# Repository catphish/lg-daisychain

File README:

PLEASE NOTE: THIS PROJECT HAS BEEN REPLACED BY https://github.com/catphish/ti-daisychain-bms

BMS and CAN interface for bq76PL455A
====================================

This module permits batteries with bq76PL455A based slave boards to be balanced and monitored. Communication
with the battery slave modules takes place via the proprietary daisychain interface on each battery module.
Up to 16 batteries can be connected in a chain.

The module supports the following functionality:
* Automatic balancing of all cells in the chain
* Pack and cell voltages transmitted on CAN bus
* Temperatures transmitted via CAN bus
* Balancing target can be set via CAN or standalone

Standlone Balancing
===================

With jumper CONF2 open, the module will operate in standalone balancing mode. It will regularly monitor the
voltage of all attached cells, and will bleed any cell that meets BOTH of the following conditions.

* Voltage exceeds 4.0V
* Voltage is more than 10mV higher than the voltage of the lowest cell in the pack

For thermal safety, only one cell (wit the highest voltage) per battery will be discharged at a time.

CAN Balancing
=============

With jumper CONF2 closed, balancing is controlled by CAN bus messages. The module will bleed all cells
in the pack that exceed the voltage specified in the appropriate CAN message. Balancing halts after one
second, so messages must be received at least once per second to ensure continuous balancing. CAN messages
are docuented below.

For thermal safety, only one cell (wit the highest voltage) per battery will be discharged at a time.

Monitoring
==========

In all operating modes, the total pack voltage, individual cell voltages, and battery temperatures
are transmitted on the CAN bus. This can be used for external monitoring or to allow a third party
control unit to make decisions about balancing, charging, and safety limits. CAN messages are
docuented below.

Connections
===========

The following connections should be made. Each pair of wires should be twisted together (approx 360 degrees per inch).

1.CANL - Connect this to your CAN bus. On early boards this is mislabeled CANH.
2.CNAH - Connect this to your CAN bus. On early boards this is mislabeled CANL.
3.+12v - Positive power supply. This can be connected to a normal vehicle 12v supply or any power supply between 4v and 15v.
4.GND  - Connect to your common low voltage ground.

If you are using Arduino, all 4 connections can simply go to an Arduino CAN shield.

BATT - This should be connected to the battery chain. Only pins 1 & 2 are required. They
       should be twisted together in the same way as the CAN wiring. OEM cables are compatible.

1 ------------ 1
2 ------------ 2
3              3 (Connection not required but may be beneficial to cable strength)
4              4 (Connection not required but may be beneficial to cable strength)

Jumpers
=======

CAN_TERM - This jumper should be connected if this board is the final device in your CAN bus. Connect it if you
           are connecting direcly to one other device such as an Arduino. This will connect a 120 Ohm resistor
           between CANL and CANH.

CONF1    - If you intend to use two of these devices on the CAN bus, connect this jumper on the second device.
           This will change the CAN ID to avoid conflicts.

CONF2    - CAN controlled balancing. Close this jumper to disable the default policy of 4.0V and 10mV and instead
           allow balancing to be controlled via CAN bus.

CAN Messages Transmitted
========================

The adapter will transmit CAN messages in the following format:

ID      : 0x4f0 (0x4f1 if Jumper CONF1 is connected)
Byte 0  : Module ID (0-15)
Byte 1  : Cell ID (Measurements 0-15 of each module are cell voltages)
Byte 2-3: Cell voltage where 0x0000 is 0.0v and 0xffff is 5.0v. Big endian.

ID      : 0x4f0 (0x4f1 if Jumper CONF1 is connected)
Byte 0  : Module ID (0-15)
Byte 1  : Temperature sensor ID (Measurements 16-23 of each module are temperatures)
Byte 2-3: Outer temperature of battery module. Big endian. See table below for details.

ID      : 0x4f0 (0x4f1 if Jumper CONF1 is connected)
Byte 0  : Module ID (0-15)
Byte 1  : 0xff
Byte 2-3: Balancing bitmap. Identifies which cells are currently being dissharged. LSB is cell 0.

ID      : 0x4f0 (0x4f1 if Jumper CONF1 is connected)
Byte 0  : 0xff (Module 0xff is the adapter itself)
Byte 1  : 0xfe (Measurement ID 0xfe is pack voltage)
Byte 2-5: Pack voltage where 0x0000 is 0.0v and 0xffff is 5.0v. Big endian.

ID      : 0x4f0 (0x4f1 if Jumper CONF1 is connected)
Byte 0  : 0xff (Module 0xff is the adapter itself)
Byte 1  : 0xff (Measurement ID 0xff is status)
Byte 2  : Number of modules detected
Byte 3  : Communication error counter. If a module fails to respond, this counter is incremented and the whole chain is reset.

Additional sensors
==================

ID      Info
--      ----
16      AUX7 - Unknown - probably internal battery temperature sensor. Scale unknown.
17      External NTC - negative side.
18      External NTC - positive side.
19      PCB Temerature. Scale unknown but values above 1v (13107) are safe. Balancing is disabled by the adapter below this value.
20      PCB Temerature. Scale unknown but values above 1v (13107) are safe. Balancing is disabled by the adapter below this value.
21      PCB Temerature. Scale unknown but values above 1v (13107) are safe. Balancing is disabled by the adapter below this value.
22      PCB Temerature. Scale unknown but values above 1v (13107) are safe. Balancing is disabled by the adapter below this value.
23      AUX0 - probably unused. Reads close to 0v

External NTC sesors
===================

The following calculation can be used to convert the readong for an External NTC to a temperature:

float temperature(uint16_t adc) {
  float r = 0.0000000347363427499292f * adc * adc - 0.001025770762903f * adc + 2.68235340614337f;
  float t = log(r) * -30.5280964239816f + 95.6841501312447f;
  return t;
}

This code will not work for the PCB temperature sensors and will probably not work for AUX7.

CAN Messages Received
=====================

The adapter listens for CAN messages in the following format. This message will instruct cells in all modules with a measured
voltage above the specified voltage to self-discharge for a period of 1 second. The specified voltage would usually be the
voltage of the most discharged cell in the chain. This message must be received at least once per second (2Hz recommended) to
balance continuously. Note: For thermal safety, only one cell with the highest volage in each module will be discharged at a
time, but in time, all cells will discharge to the requested voltage.

ID      : 0x4f8 (note: all adapters will act regardless of CONF1 jumper)
Byte 0  : 0x00 (Balance)
Byte 1-2: Cell voltage threshold where 0x0000 is 0.0v and 0xffff is 5.0v

The following message will attempt to reset and re-identify all modules in the chain.
ID      : 0x4f8 (note: all adapters will reset regardless of CONF1 jumper)
Byte 0  : 0x01 (Reset)

The following message will cause the module and all slave modules to sleep in a low power state until a reset message is received
ID      : 0x4f8 (note: all adapters will sleep regardless of CONF1 jumper)
Byte 0  : 0x02 (Sleep)

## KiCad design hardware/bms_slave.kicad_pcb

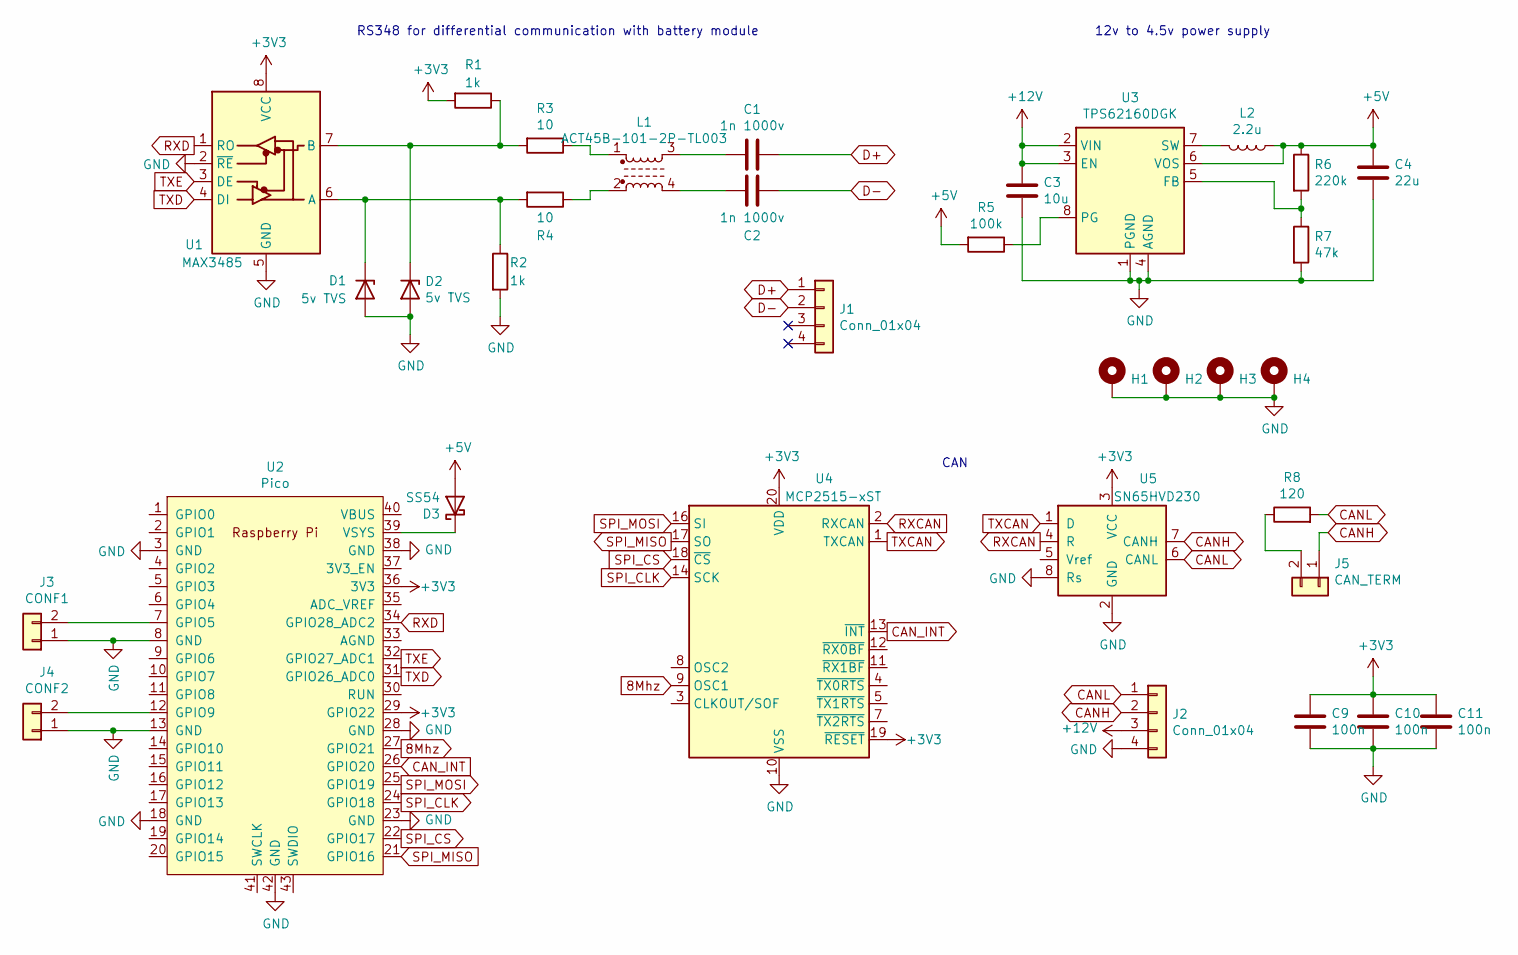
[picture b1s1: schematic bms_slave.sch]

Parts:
C1, C2: 1n 1000v; C_1206_3216Metric; LCSC C1941
C3: 10u; C_1210_3225Metric; LCSC C77102
C4: 22u; C_1206_3216Metric; LCSC C97950
C9, C10, C11: 100n; C_0603_1608Metric; LCSC C14663
D1, D2: 5v TVS; SOD882; LCSC C85401
D3: SS54; D_SMA; LCSC C22452
H1, H2, H3, H4: MountingHole; MountingHole_3.2mm_M3_Pad
J1, J2: Conn_01x04; SM04B1-CPTK-1A
J3: CONF1; PinHeader_1x02_P2.54mm_Vertical
J4: CONF2; PinHeader_1x02_P2.54mm_Vertical
J5: CAN_TERM; PinHeader_1x02_P2.54mm_Vertical
L1: ACT45B-101-2P-TL003; LCSC C88056
L2: 2.2u; 1227ASH100MP2; LCSC C435389
R1, R2: 1k; R_0603_1608Metric; LCSC C21190
R3, R4: 10; R_0603_1608Metric; LCSC C22859
R5: 100k; R_0603_1608Metric; LCSC C25803
R6: 220k; R_0603_1608Metric; LCSC C22961
R7: 47k; R_0603_1608Metric; LCSC C25819
R8: 120; R_1206_3216Metric; LCSC C17909
U1: MAX3485; SOP-8_3.9x4.9mm_P1.27mm; LCSC C18148
U2: Pico; RPi_Pico_SMD_TH
U3: TPS62160DGK; MSOP-8_3x3mm_P0.65mm; LCSC C60726
U4: MCP2515-xST; TSSOP-20_4.4x6.5mm_P0.65mm; LCSC C15193
U5: SN65HVD230; SOIC-8_3.9x4.9mm_P1.27mm; LCSC C12084

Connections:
8Mhz: U2.27 (GPIO21), U4.9 (OSC1)
+3V3: C9.1, C10.1, C11.1, R1.2, U1.8 (VCC), U2.29 (GPIO22), U2.36 (3V3), U4.19 (~RESET), U4.20 (VDD), U5.3 (VCC)
+5V: C4.1, D3.2 (A), L2.1, R5.2, R6.1, U3.6 (VOS)
+12V: C3.1, J2.3, U3.2 (VIN), U3.3 (EN)
CANH: J2.2, J5.1, U5.7 (CANH)
CANL: J2.1, R8.2, U5.6 (CANL)
CAN_INT: U2.26 (GPIO20), U4.13 (~INT)
D+: C1.1, J1.1
D-: C2.1, J1.2
GND: C3.2, C4.2, C9.2, C10.2, C11.2, D1.2 (A), D2.2 (A), H1.1, H2.1, H3.1, H4.1, J2.4, J3.1, J4.1, R2.2, R7.2, U1.2 (~RE), U1.5 (GND), U2.3 (GND), U2.8 (GND), U2.13 (GND), U2.18 (GND), U2.23 (GND), U2.28 (GND), U2.38 (GND), U2.42 (GND), U3.1 (PGND), U3.4 (AGND), U4.10 (VSS), U5.2 (GND), U5.8 (Rs)
unnamed: C1.2, L1.3
unnamed: C2.2, L1.4
unnamed: D1.1 (K), R2.1, R4.2, U1.6 (A)
unnamed: D2.1 (K), R1.1, R3.2, U1.7 (B)
unnamed: D3.1 (K), U2.39 (VSYS)
unnamed: J3.2, U2.7 (GPIO5)
unnamed: J4.2, U2.12 (GPIO9)
unnamed: J5.2, R8.1
unnamed: L1.1, R3.1
unnamed: L1.2, R4.1
unnamed: L2.2, U3.7 (SW)
unnamed: R5.1, U3.8 (PG)
unnamed: R6.2, R7.1, U3.5 (FB)
RXCAN: U4.2 (RXCAN), U5.4 (R)
RXD: U1.1 (RO), U2.34 (GPIO28_ADC2)
SPI_CLK: U2.24 (GPIO18), U4.14 (SCK)
SPI_CS: U2.22 (GPIO17), U4.18 (~CS)
SPI_MISO: U2.21 (GPIO16), U4.17 (SO)
SPI_MOSI: U2.25 (GPIO19), U4.16 (SI)
TXCAN: U4.1 (TXCAN), U5.1 (D)
TXD: U1.4 (DI), U2.31 (GPIO26_ADC0)
TXE: U1.3 (DE), U2.32 (GPIO27_ADC1)

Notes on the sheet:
RS348 for differential communication with battery module
12v to 4.5v power supply
CAN

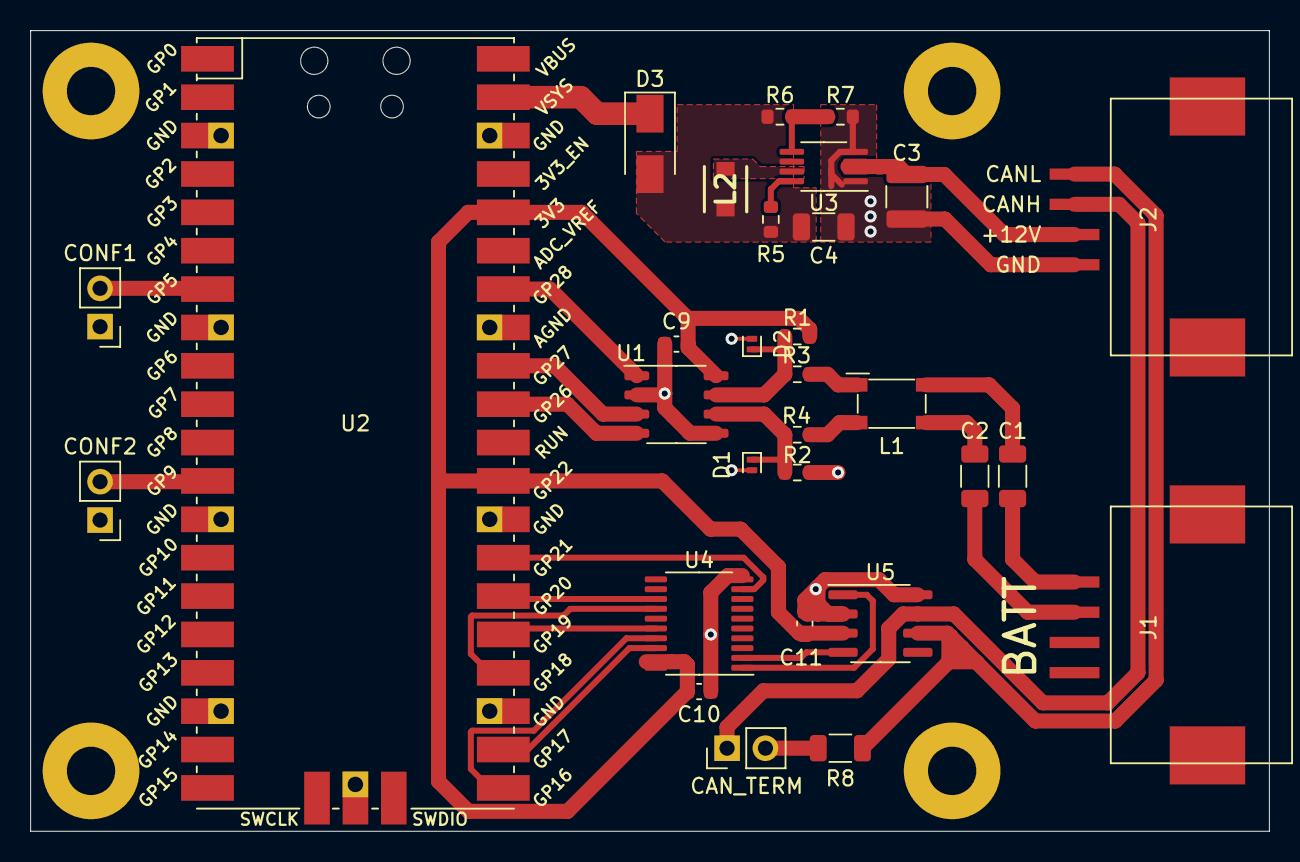
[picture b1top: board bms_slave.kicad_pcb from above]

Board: 2 copper layers, 82.0 x 53.0 mm, 34 parts (0 on the bottom side), 32 nets.

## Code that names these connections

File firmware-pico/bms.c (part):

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
// Define pins for SPI (to CAN)
#define SPI_PORT spi0
#define SPI_MISO 16
#define SPI_CS   17
#define SPI_CLK  18
#define SPI_MOSI 19
#define CAN_CLK  21 // 8MHz clock for CAN

// Define config pins
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void SPI_configure() {
  spi_init(SPI_PORT, 1000000);
  spi_set_format(SPI_PORT, 8, 0,0,SPI_MSB_FIRST);
  gpio_set_function(SPI_MISO, GPIO_FUNC_SPI);
  gpio_set_function(SPI_MOSI, GPIO_FUNC_SPI);
  gpio_set_function(SPI_CLK, GPIO_FUNC_SPI);
  gpio_init(SPI_CS);
  gpio_set_dir(SPI_CS, GPIO_OUT);
  gpio_put(SPI_CS, 1);
}

void CAN_reset() {
  gpio_put(SPI_CS, 0);
  spi_write_blocking(SPI_PORT, (uint8_t[]){CMD_RESET},1);
  gpio_put(SPI_CS, 1);
  busy_wait_us(100);
}

uint8_t CAN_reg_read(uint8_t reg) {
  uint8_t data;
  gpio_put(SPI_CS, 0);
  spi_write_blocking(SPI_PORT, (uint8_t[]){CMD_READ, reg}, 2);
  spi_read_blocking(SPI_PORT, 0, &data, 1);
  gpio_put(SPI_CS, 1);
  return(data);
}

void CAN_reg_write(uint8_t reg, uint8_t val) {
  gpio_put(SPI_CS, 0);
  spi_write_blocking(SPI_PORT, (uint8_t[]){CMD_WRITE, reg, val}, 3);
  gpio_put(SPI_CS, 1);
}

void CAN_reg_modify(uint8_t reg, uint8_t mask, uint8_t val) {
  gpio_put(SPI_CS, 0);
  busy_wait_us(2);
  spi_write_blocking(SPI_PORT, (uint8_t[]){CMD_MODIFY, reg, mask, val}, 4);
  busy_wait_us(2);
  gpio_put(SPI_CS, 1);
}

void CAN_configure(uint16_t id) {
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
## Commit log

2021-11-06 initial commit of example arduino master and documentation
2021-11-08 add correct arduino file
2021-11-08 improve balancing comments
2021-11-14 add hardware and firmware sources
2021-11-24 add reset command
2021-11-26 remove CAN, output votages and temps only
2021-11-26 balancing
2021-11-28 fix balance threshold
2021-11-28 tidy comments
2021-11-28 more comments
2021-11-28 use better constants
2021-11-29 change usb output format, change differential threshold to 10mV
2021-12-06 low power sleep when not balancing
2021-12-06 print error message on communication error condition
2021-12-06 replace long busy wait with low power sleep
2021-12-08 tidy up standalone mode
2021-12-08 add asterisk next to bleeding cells
2021-12-10 add CAN, add jumper to select standalone vs CAN, remove unused code
2021-12-10 CAN fixes
2021-12-10 invert mode jumper, fix pack voltage display
2021-12-10 add arduino CAN exaple and update documentation for dual mode firmware
2021-12-29 new compact USB serial output format
2022-01-04 simpler CAN timeout
2022-01-04 simple CAN output
2022-01-04 tweak documentation to reflect 4.12V threshold
2022-01-04 add binary file
